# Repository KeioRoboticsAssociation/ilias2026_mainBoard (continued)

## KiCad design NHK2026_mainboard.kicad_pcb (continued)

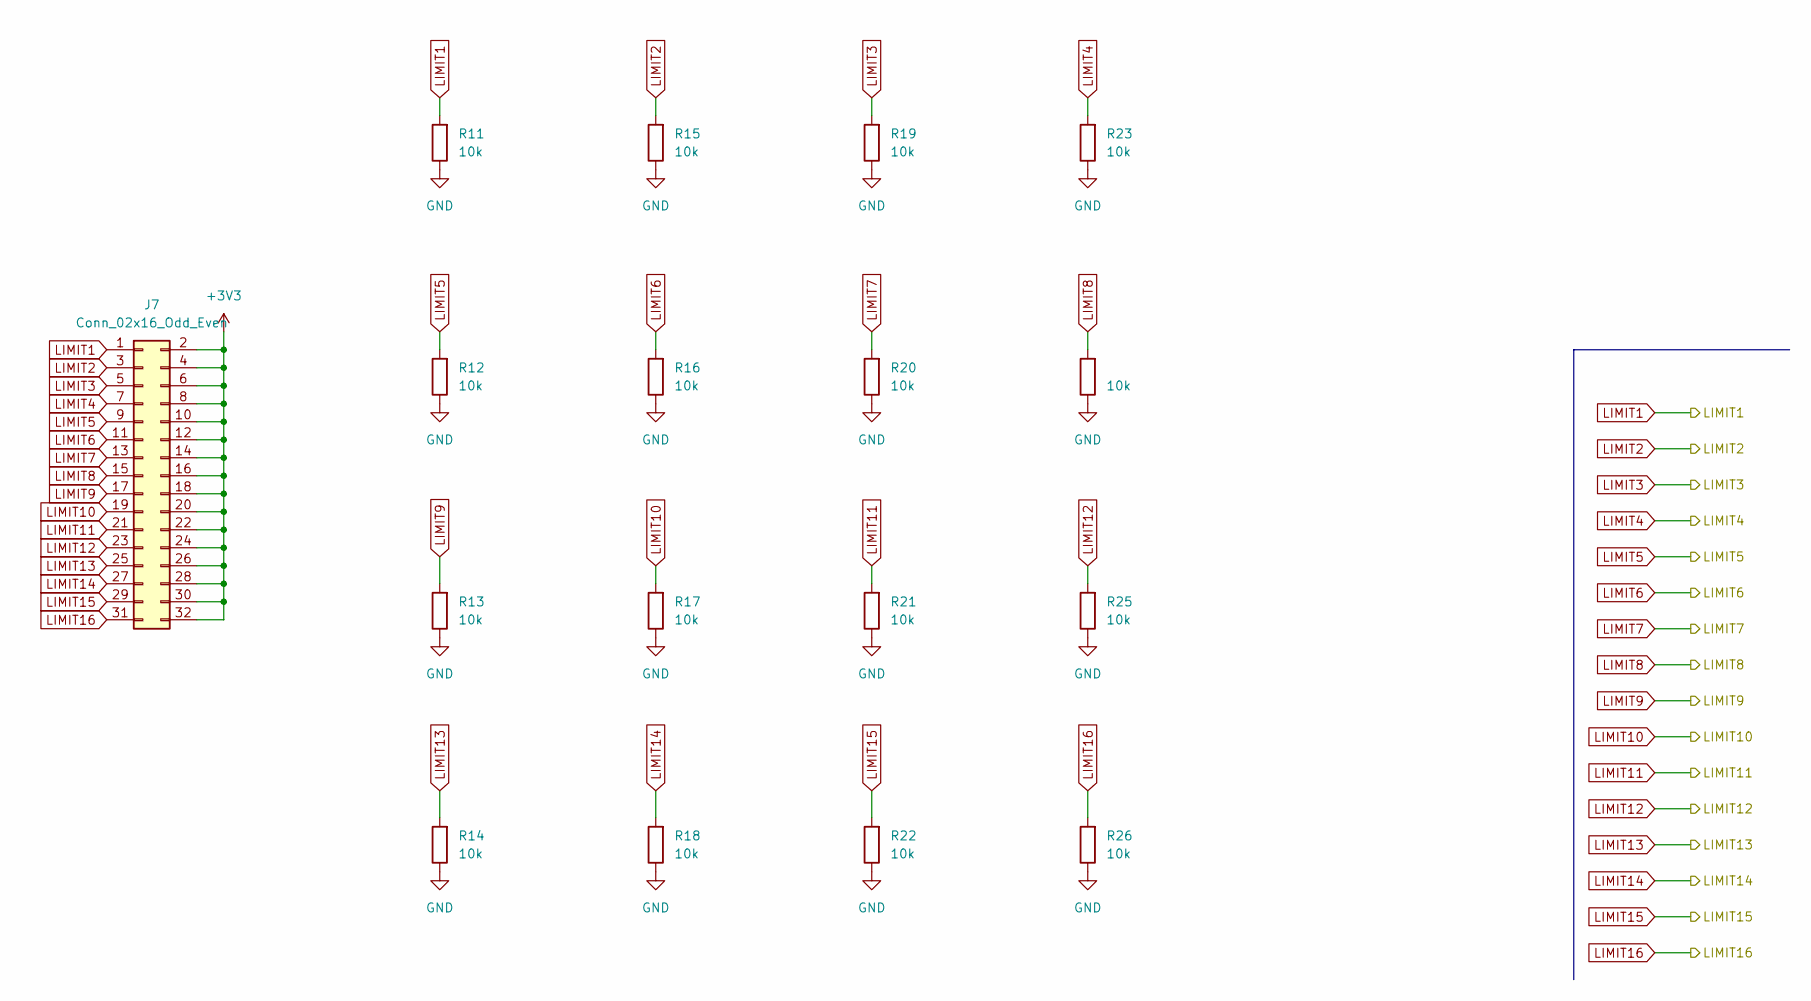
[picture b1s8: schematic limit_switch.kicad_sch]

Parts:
J7: Conn_02x16_Odd_Even; PinHeader_2x16_P2.54mm_Vertical
R11, R12, R13, R14, R15, R16, R17, R18, R19, R20, R21, R22, R23, R24, R25, R26: 10k; R_0603_1608Metric_Pad0.98x0.95mm_HandSolder

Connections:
+3V3: J7.2, J7.4, J7.6, J7.8, J7.10, J7.12, J7.14, J7.16, J7.18, J7.20, J7.22, J7.24, J7.26, J7.28, J7.30, J7.32; also elsewhere on the board
GND: R11.1, R12.1, R13.1, R14.1, R15.1, R16.1, R17.1, R18.1, R19.1, R20.1, R21.1, R22.1, R23.1, R24.1, R25.1, R26.1; also elsewhere on the board
LIMIT1: J7.1, R11.2; also elsewhere on the board
LIMIT2: J7.3, R15.2; also elsewhere on the board
LIMIT3: J7.5, R19.2; also elsewhere on the board
LIMIT4: J7.7, R23.2; also elsewhere on the board
LIMIT5: J7.9, R12.2; also elsewhere on the board
LIMIT6: J7.11, R16.2; also elsewhere on the board
LIMIT7: J7.13, R20.2; also elsewhere on the board
LIMIT8: J7.15, R24.2; also elsewhere on the board
LIMIT9: J7.17, R13.2; also elsewhere on the board
LIMIT10: J7.19, R17.2; also elsewhere on the board
LIMIT11: J7.21, R21.2; also elsewhere on the board
LIMIT12: J7.23, R25.2; also elsewhere on the board
LIMIT13: J7.25, R14.2; also elsewhere on the board
LIMIT14: J7.27, R18.2; also elsewhere on the board
LIMIT15: J7.29, R22.2; also elsewhere on the board
LIMIT16: J7.31, R26.2; also elsewhere on the board

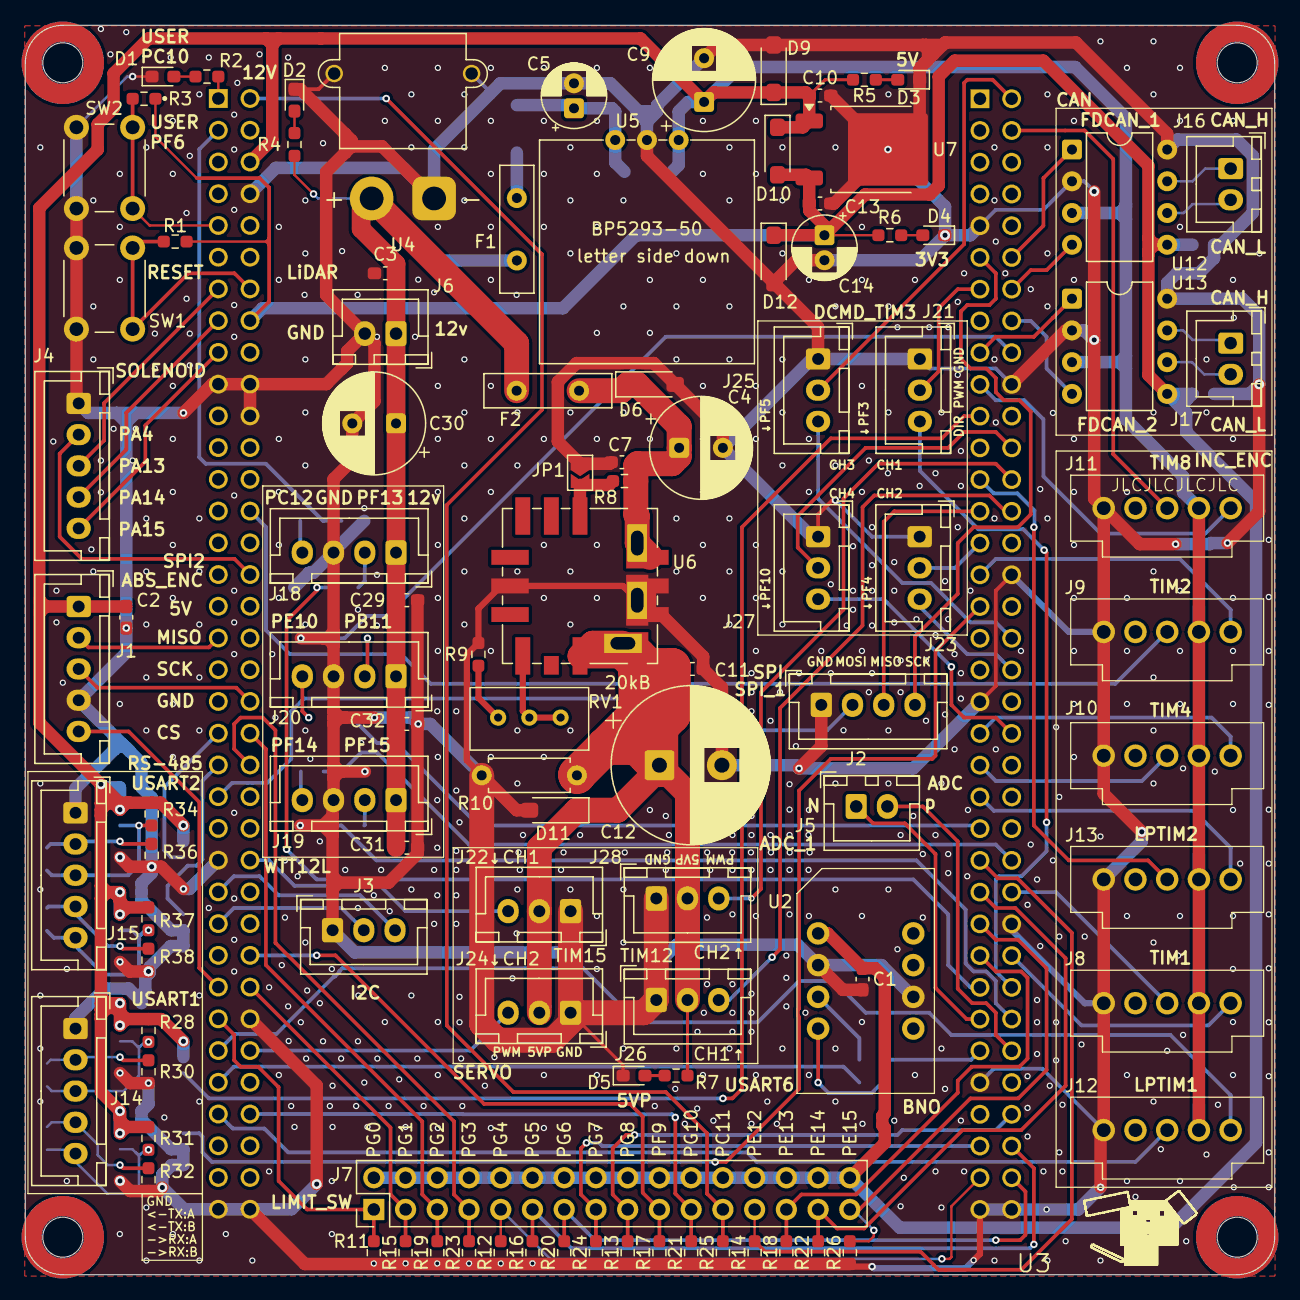
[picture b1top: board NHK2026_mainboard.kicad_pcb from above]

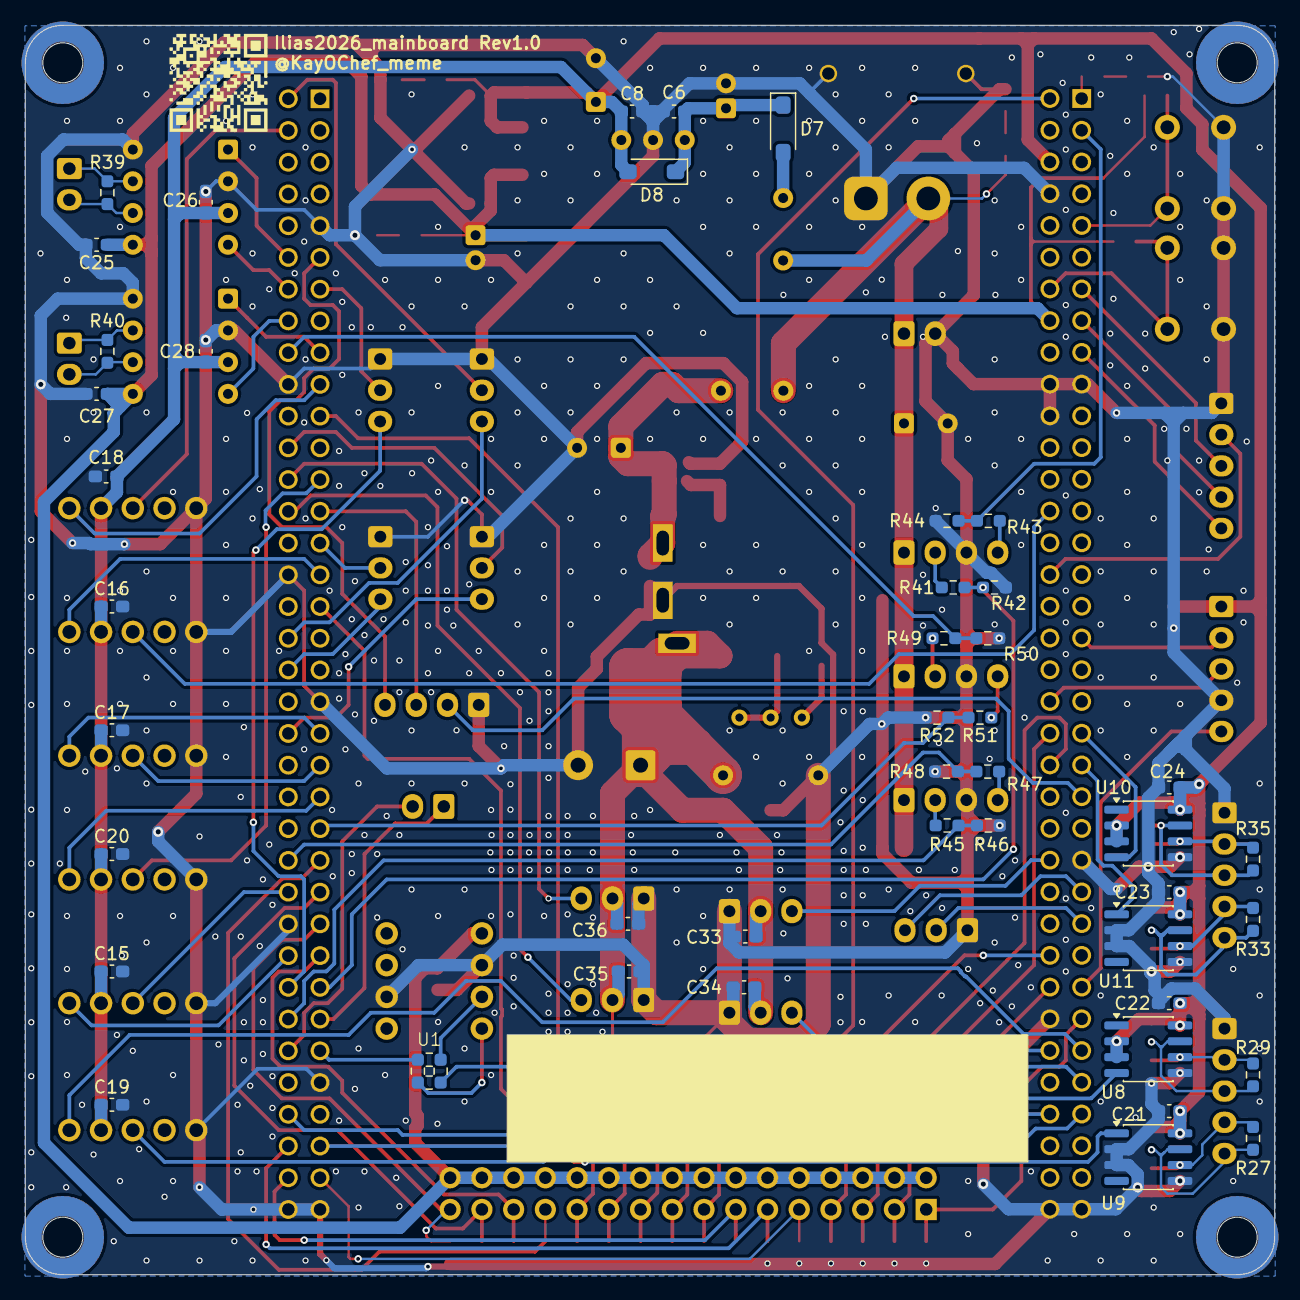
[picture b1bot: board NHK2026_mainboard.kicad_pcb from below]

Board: 2 copper layers, 100.0 x 100.0 mm, 148 parts (45 on the bottom side), 109 nets.

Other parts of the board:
ref**: val**; ROGIKEN

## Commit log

2025-10-06 second
2025-10-06 今日はここまで
2025-10-08 恥を捨て豊橋スタイル丸パクリ
2025-10-08 回路図だいたい完成
2025-10-09 何こっち見てんだよ
2025-10-09 配置だいたい完了
2025-10-12 配線だいたい完了
2025-10-12 メイン基板完成
2025-10-12 QRコードと回路図pdfを追加
2025-10-14 製造番号位置指定
